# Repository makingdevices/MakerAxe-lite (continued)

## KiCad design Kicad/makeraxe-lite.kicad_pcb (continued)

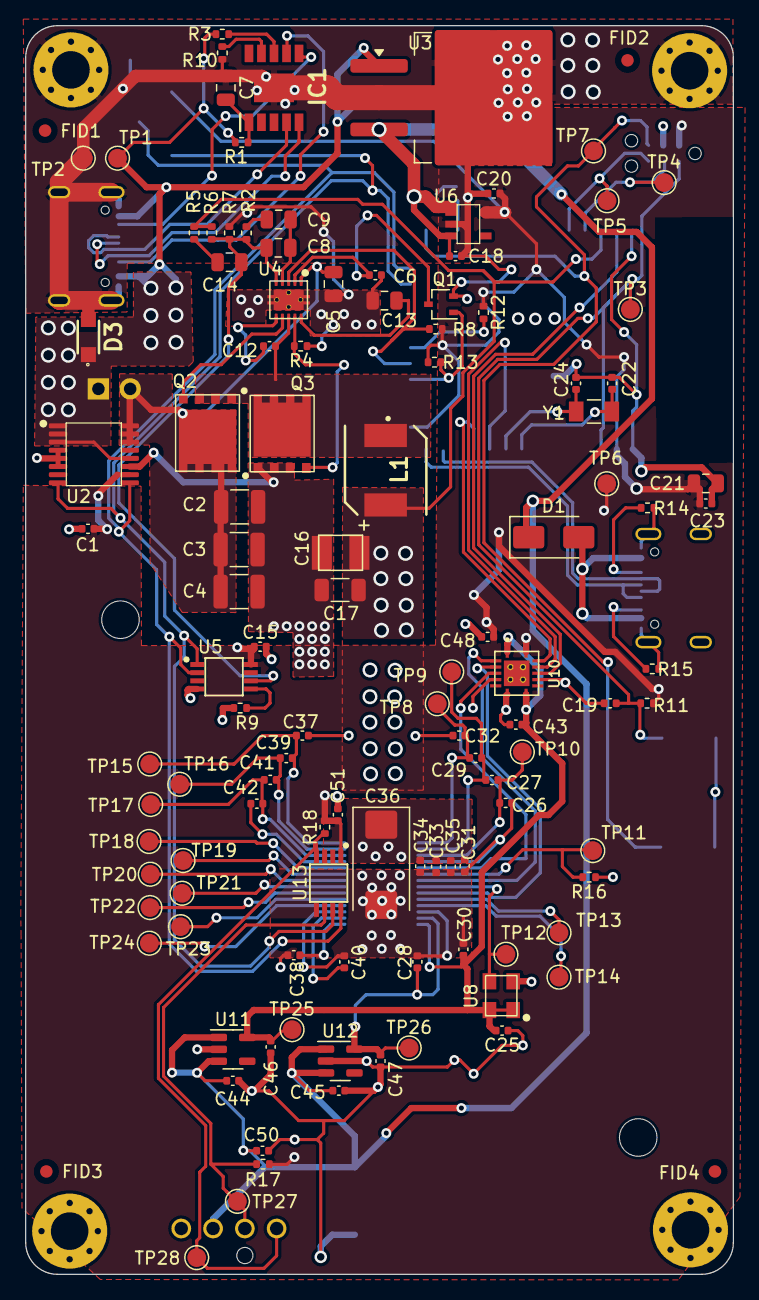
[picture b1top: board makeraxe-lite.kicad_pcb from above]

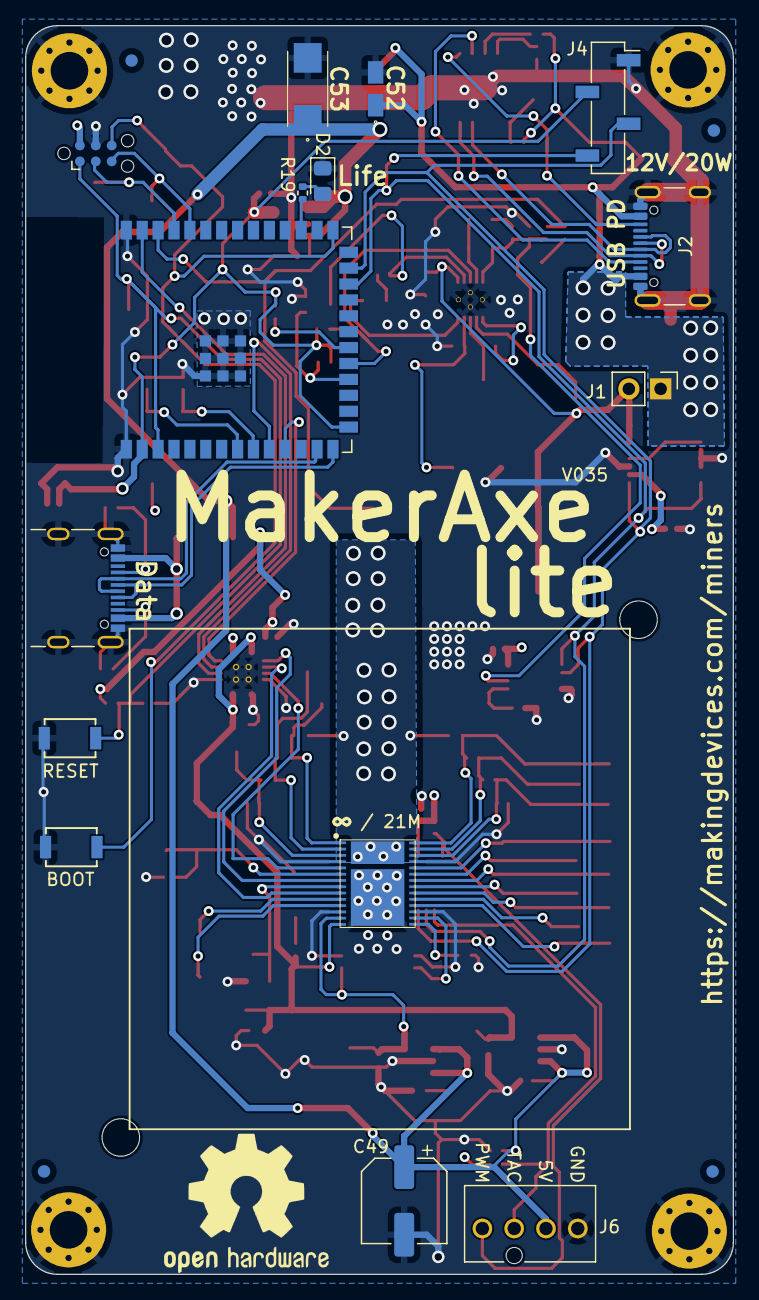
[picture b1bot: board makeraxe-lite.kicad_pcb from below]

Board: 2 copper layers, 56.5 x 99.8 mm, 141 parts (19 on the bottom side), 71 nets.

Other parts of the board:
R12: 1M; R_0402_1005Metric
R13, R16: 10k; R_0402_1005Metric
R17: 5.6k; R_0402_1005Metric

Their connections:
/3V3: R12.1, R13.1, R17.2; also elsewhere on the board
/ESP32/PLUG_SENSE: R12.2; also elsewhere on the board
/ESP32/PWR_EN: R13.2; also elsewhere on the board
/Fan/FAN_TACH: R17.1; also elsewhere on the board

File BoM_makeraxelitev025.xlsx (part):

PCB Parts
Reference | Value | Datasheet | Footprint | Qty | Unit Price | Total Price | Generic? | LCSC ref | LCSC | Digikey Ref | Digikey | DNP
C1,C15,C18,C19,C20,C26,C27,C28,C29,C30,C32,C34,C35,C37,C38,C39,C40,C41,C42,C44,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 | 1uF - 50V |  | Capacitor_SMD:C_0402_1005Metric | 23 | 2.29E-2 | 0.52670000000000006 | Yes | C1518208 | https://www.lcsc.com/product-detail/Multilayer-Ceramic-Capac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
C2,C3,C4 | 47uF - 25V | ~ | Capacitor_SMD:C_1210_3225Metric | 3 | 0.31680000000000003 | 0.95040000000000013 | Yes | C90142 | https://www.lcsc.com/product-detail/Multilayer-Ceramic-Capac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
C5,C7 | 1uF -50V | ~ | Capacitor_SMD:C_0805_2012Metric | 2 | 8.3999999999999995E-3 | 1.6799999999999999E-2 | Yes | C28323 | https://www.lcsc.com/product-detail/Multilayer-Ceramic-Capac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
C6 | 3.3nF -50V | ~ | Capacitor_SMD:C_0402_1005Metric | 1 | 1.1599999999999999E-2 | 1.1599999999999999E-2 | Yes | C1518207 | https://www.lcsc.com/product-detail/Multilayer-Ceramic-Capac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
C8 | 180pF -50V | ~ | Capacitor_SMD:C_0805_2012Metric | 1 | 8.2000000000000007E-3 | 8.2000000000000007E-3 | Yes | C113826 | https://www.lcsc.com/product-detail/Multilayer-Ceramic-Capac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
C9 | 1.5nF - 50V | ~ | Capacitor_SMD:C_0805_2012Metric | 1 | 5.0000000000000001E-3 | 5.0000000000000001E-3 | Yes | C107142 | https://www.lcsc.com/product-detail/Multilayer-Ceramic-Capac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
C10 | 0.47uF | ~ | Capacitor_SMD:C_0805_2012Metric | 1 | 1.1299999999999999E-2 | 1.1299999999999999E-2 | Yes | C106843 | https://www.lcsc.com/product-detail/Multilayer-Ceramic-Capac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
C11 | 22uF | ~ | Capacitor_SMD:C_0805_2012Metric | 1 | 2.0500000000000001E-2 | 2.0500000000000001E-2 | Yes | C602037 | https://www.lcsc.com/product-detail/Multilayer-Ceramic-Capac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
C12,C23,C25,C31,C33,C43,C48,C50,C51 | 0.1uF |  | Capacitor_SMD:C_0402_1005Metric | 9 | 2.5000000000000001E-3 | 2.2499999999999999E-2 | Yes | C131394 | https://www.lcsc.com/product-detail/Multilayer-Ceramic-Capac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
C13,C21 | 10uF |  | Capacitor_SMD:C_0805_2012Metric | 2 | 6.1800000000000001E-2 | 0.1236 | Yes | C440198 | https://www.lcsc.com/product-detail/Multilayer-Ceramic-Capac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
C14 | 470pF | ~ | Capacitor_SMD:C_0805_2012Metric | 1 | 7.7999999999999996E-3 | 7.7999999999999996E-3 | Yes | C1822 | https://www.lcsc.com/product-detail/Multilayer-Ceramic-Capac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
C16 | 220uF | https://media.digikey.com/pdf/Data%20Sheets/Panasonic%20Capa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 | bitaxe:CAP_2R5TPE220MAFB | 1 | 0.25380000000000003 | 0.25380000000000003 | Alternative?? | C2976916 | https://www.lcsc.com/product-detail/Tantalum-Capacitors_CEC-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
C17 | 100uF - 10V | ~ | Capacitor_SMD:C_1206_3216Metric | 1 | 0.15659999999999999 | 0.15659999999999999 | Yes | C883598 | https://www.lcsc.com/product-detail/Multilayer-Ceramic-Capac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
C22,C24 | 6.8pF | ~ | Capacitor_SMD:C_0402_1005Metric | 2 | 1.1999999999999999E-3 | 2.3999999999999998E-3 | Yes | C5186887 | https://www.lcsc.com/product-detail/Multilayer-Ceramic-Capac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
C36 | 330uF | ~ | Capacitor_Tantalum_SMD:CP_EIA-7343-31_Kemet-D_Pad2.25x2.55mm_HandSolder | 1 | 1.0355000000000001 | 1.0355000000000001 |  | C1965141 | https://www.lcsc.com/product-detail/Tantalum-Capacitors_Vish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
C49 | 220uF | ~ | Capacitor_SMD:CP_Elec_6.3x7.7 | 1 | 8.3400000000000002E-2 | 8.3400000000000002E-2 | Alternative?? | C25503905 | https://www.lcsc.com/product-detail/Polymer-Aluminum-Capacit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
D1 | SS310 | https://www.mccsemi.com/pdf/Products/SK32A-L-SK310A-L(DO-214AC).pdf | Diode_SMD:D_SMA | 1 | 6.5000000000000002E-2 | 6.5000000000000002E-2 | Yes | C2898938 | https://www.lcsc.com/product-detail/Schottky-Diodes_YFW-SS31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
D2 | LED | ~ | LED_SMD:LED_0805_2012Metric_Pad1.15x1.40mm_HandSolder | 1 | 6.0699999999999997E-2 | 6.0699999999999997E-2 | Yes | C264427 | https://www.lcsc.com/product-detail/LED-Indication-Discrete_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
D3 | PTVS20VS1UR,115 | https://assets.nexperia.com/documents/data-sheet/PTVSXS1UR_SER.pdf | bitaxe:SOD123W | 1 | 0.18770000000000001 | 0.18770000000000001 |  | C461164 | https://www.lcsc.com/product-detail/ESD-and-Surge-Protection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
IC1 | CH224K | https://datasheet.lcsc.com/lcsc/2204251615_WCH-Jiangsu-Qin-H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 | SOP100P600X180-11N | 1 | 0.47749999999999998 | 0.47749999999999998 |  | C970725 | https://www.lcsc.com/product-detail/USB-PD_WCH-Jiangsu-Qin-H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
J2,J5 | USB_C_Receptacle_USB2.0 | https://gct.co/connector/usb4105 | Connector_USB:USB_C_Receptacle_GCT_USB4105-xx-A_16P_TopMnt_Horizontal | 2 |  | 0 |  |  |  | 2073-USB4105-GF-ACT-ND | https://www.digikey.es/es/products/detail/gct/USB4105-GF-A/1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
J4 | Conn_01x04 | ~ | Connector_PinSocket_2.54mm:PinSocket_1x04_P2.54mm_Vertical_SMD_Pin1Right | 1 |  | 0 |  |  |  | NPTC041KFXC-RC |  | DNP
J6 | Conn_01x04 | ~ | bitaxe:470531000 | 1 | 0.18970000000000001 | 0.18970000000000001 | Yes | C240840 | https://www.lcsc.com/product-detail/Wire-To-Board-Connector_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
L1 | SPM6530T-R47M-HZ | https://product.tdk.com/system/files/dam/doc/product/inducto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 | SPM6530 | 1 | 0.37290000000000001 | 0.37290000000000001 | Alternative?? | C3040345 | https://www.lcsc.com/product-detail/Power-Inductors_cjiang-C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
Q1 | 2N7002K | https://www.diodes.com/assets/Datasheets/ds30896.pdf | Package_TO_SOT_SMD:SOT-323_SC-70 | 1 | 0.1104 | 0.1104 | Yes | C266797 | https://www.lcsc.com/product-detail/MOSFETs_onsemi-2N7002KW_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
Q2,Q3 | CSD17311Q5 | https://www.ti.com/lit/ds/symlink/csd17311q5.pdf | bitaxe:CSD17311Q5 | 2 | 1.1518999999999999 | 2.3037999999999998 |  | C139640 | https://www.lcsc.com/product-detail/MOSFETs_Texas-Instrument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
R1 | 1k | ~ | Resistor_SMD:R_0402_1005Metric | 1 | 5.9999999999999995E-4 | 5.9999999999999995E-4 | Yes | C106235 | https://www.lcsc.com/product-detail/Chip-Resistor-Surface-Mo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
R2 | 3.83k | ~ | Resistor_SMD:R_0402_1005Metric | 1 | 5.0000000000000001E-4 | 5.0000000000000001E-4 | Yes | C67236 | https://www.lcsc.com/product-detail/Chip-Resistor-Surface-Mo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
R3,R8,R11,R13,R16,R18 | 10K | ~ | Resistor_SMD:R_0402_1005Metric | 6 | 5.0000000000000001E-4 | 3.0000000000000001E-3 | Yes | C60490 | https://www.lcsc.com/product-detail/Chip-Resistor-Surface-Mo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
R4 | 4.12k | ~ | Resistor_SMD:R_0402_1005Metric | 1 | 4.0000000000000002E-4 | 4.0000000000000002E-4 | Yes | C327340 | https://www.lcsc.com/product-detail/Chip-Resistor-Surface-Mo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
R5 | 1.33k | ~ | Resistor_SMD:R_0402_1005Metric | 1 | 5.4999999999999997E-3 | 5.4999999999999997E-3 | Yes | C400606 | https://www.lcsc.com/product-detail/Chip-Resistor-Surface-Mo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
R6 | 4.99k | ~ | Resistor_SMD:R_0402_1005Metric | 1 | 5.0000000000000001E-4 | 5.0000000000000001E-4 | Yes | C168233 | https://www.lcsc.com/product-detail/Chip-Resistor-Surface-Mo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
R7 | 3.32k | ~ | Resistor_SMD:R_0402_1005Metric | 1 | 5.0000000000000001E-4 | 5.0000000000000001E-4 | Yes | C60075 | https://www.lcsc.com/product-detail/Chip-Resistor-Surface-Mo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
R9 | 80.6k | ~ | Resistor_SMD:R_0402_1005Metric | 1 | 1E-3 | 1E-3 | Yes | C227238 | https://www.lcsc.com/product-detail/Chip-Resistor-Surface-Mo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
R10 | 0 | ~ | Resistor_SMD:R_0402_1005Metric | 1 |  |  |  | JUMPER | --Solder with tin if neccesary-- |  |  | DNP
R12 | 1M | ~ | Resistor_SMD:R_0402_1005Metric | 1 | 5.0000000000000001E-4 | 5.0000000000000001E-4 | Yes | C2909328 | https://www.lcsc.com/product-detail/Chip-Resistor-Surface-Mo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
R14,R15 | 5.1k | ~ | Resistor_SMD:R_0402_1005Metric | 2 | 5.0000000000000001E-4 | 1E-3 | Yes | C2906874 | https://www.lcsc.com/product-detail/Chip-Resistor-Surface-Mo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
R17 | 5.6k | ~ | Resistor_SMD:R_0402_1005Metric | 1 | 5.0000000000000001E-4 | 5.0000000000000001E-4 | Yes | C2909364 | https://www.lcsc.com/product-detail/Chip-Resistor-Surface-Mo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
R19 | 220 | ~ | Resistor_SMD:R_0402_1005Metric | 1 | 4.0000000000000002E-4 | 4.0000000000000002E-4 | Yes | C25151 | https://www.lcsc.com/product-detail/Chip-Resistor-Surface-Mo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
SW1,SW2 | GT-TC029B-H025-L1N | https://www.citrelay.com/Catalog%20Pages/SwitchCatalog/CS1213.pdf | bitaxe:SW_CS1213AGF260_CRS | 2 | 5.8200000000000002E-2 | 0.1164 | Yes | C843669 | https://www.lcsc.com/product-detail/Tactile-Switches_G-Switc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

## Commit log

2024-12-18 cleaning and releasing a new v0.25 board
2024-12-19 Updating Bill Of Materials
2024-12-20 no message
2024-12-26 Update to readme
2024-12-26 update readme. Update gitignore
2024-12-26 Link the gerber files
2024-12-26 License files! We are OpenSource baby!
2024-12-26 Update version for the readme
2024-12-29 update new readme
2024-12-29 update ignore file
2024-12-29 cleaning
2024-12-30 update ibom and pcb3d
2024-12-30 New renders from Blender
2025-11-05 V0.35 Release
